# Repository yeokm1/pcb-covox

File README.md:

# pcb-covox
A tiny sound card based on the Covox Speech Thing design. I have another design which adds on an LM386 amplifier which can be found [here](https://github.com/yeokm1/pcb-covox-amp/).

##PCB Design software and addons used

1. Eagle 7.5.0: I use Standard but Light should still be able to open/modify the files.

##Images

This is a revision 3 board which has a bug in the mj2135 library which is a misaligned hole. I corrected this in Revision 4 but never actually fabricated that update.

Due to my oversight, only the DB25 pin 19 is grounded whearas the standard calls for pins 18-25 to be done so. You might need to modify the design if you face problems.

##Schematic drawings
Images are exported from Eagle at 600dpi.

##Parts required
Use Libreoffice to open [pcb-covox-bom.ods](pcb-covox-bom.ods)

##References
1. [Hardware implementation references](https://blog.frantovo.cz/c/307/DAC%20%28zvukov%C3%A1%20karta%29%20pro%20LPT%20port%20a.k.a.%20Covox)
2. [Design reference](http://kb.gr8bit.ru/KB0010/GR8BIT-KB0010-Adding-multimedia-capability-covox-device.html)
3. [MJ-2135 package obtained from coqui-dip](https://github.com/open-eie/coqui-dip)

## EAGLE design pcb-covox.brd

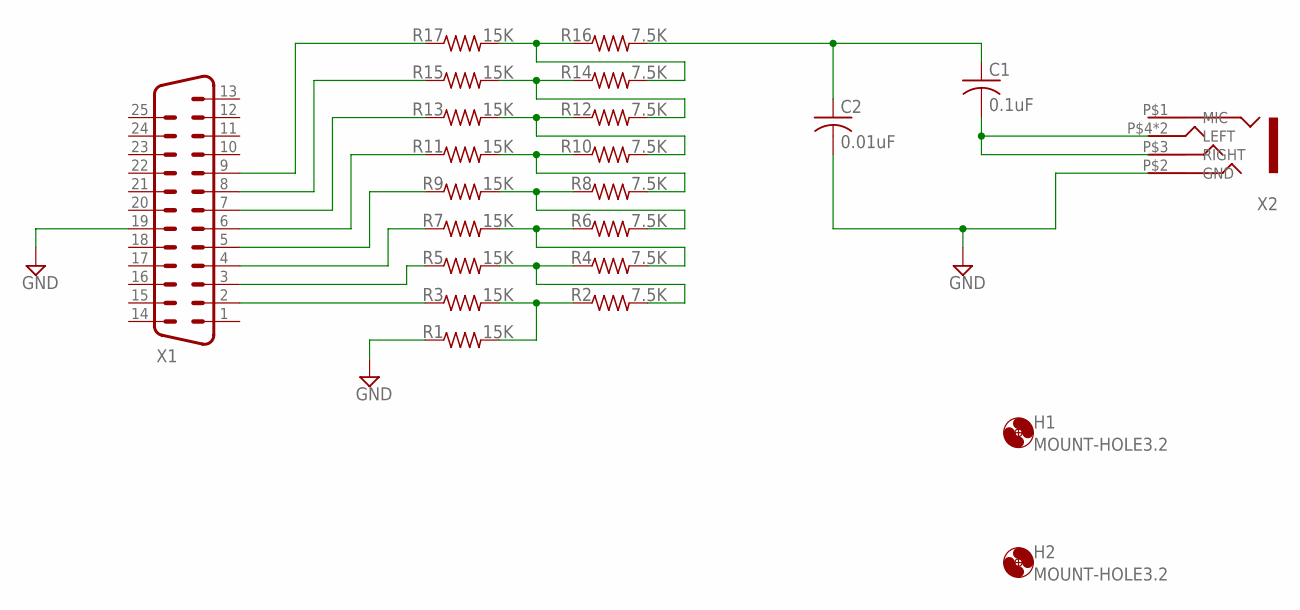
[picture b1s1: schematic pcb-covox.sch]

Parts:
C1: 0.1uF; C0805
C2: 0.01uF; C0805
H1, H2: MOUNT-HOLE3.2; 3,2
R1, R3, R5, R7, R9, R11, R13, R15, R17: 15K; R0805
R2, R4, R6, R8, R10, R12, R14, R16: 7.5K; R0805
X1: M25HP
X2: MJ-2135MJ-2135; MJ-2135

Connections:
GND: C2.2, R1.1, X1.19, X2.P$2 (GND)
unnamed: R3.1, X1.2
unnamed: R5.1, X1.3
unnamed: R7.1, X1.4
unnamed: R9.1, X1.5
unnamed: R11.1, X1.6
unnamed: R13.1, X1.7
unnamed: R15.1, X1.8
unnamed: R17.1, X1.9
unnamed: R1.2, R2.1, R3.2
unnamed: R2.2, R4.1, R5.2
unnamed: R4.2, R6.1, R7.2
unnamed: R6.2, R8.1, R9.2
unnamed: R8.2, R10.1, R11.2
unnamed: R10.2, R12.1, R13.2
unnamed: R12.2, R14.1, R15.2
unnamed: R14.2, R16.1, R17.2
unnamed: C1.1, C2.1, R16.2
unnamed: C1.2, X2.P$3 (RIGHT), X2.P$4 (LEFT), X2.P$5 (LEFT)

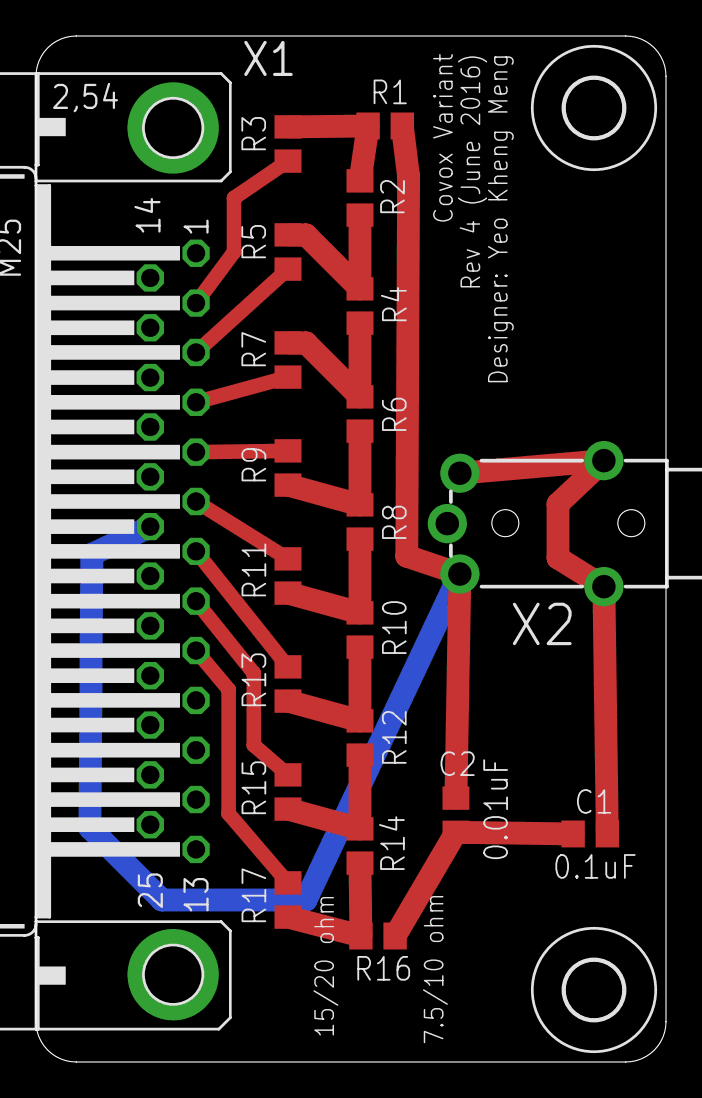
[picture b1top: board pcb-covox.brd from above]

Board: 2 copper layers, 35.0 x 57.0 mm, 23 parts (0 on the bottom side), 19 nets.

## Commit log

2016-04-14 rev 1
2016-04-14 images
2016-04-14 bom file
2016-04-27 corrected bug in size of audio connector
2016-04-29 correct drc error
2016-04-29 rev 2 gerber
2016-04-29 update to rev2 images
2016-04-29 adjust MJ-2135 value
2016-05-09 updated error in mj 2135 library
2016-05-09 rev 3 gerber
2016-05-09 update rev 3 image
2016-05-09 change directory of gerber
2016-06-17 update error in mj2135 lbr
2016-06-17 up to rev 4 for silkscreen
2016-07-02 rev4 board image
2016-07-02 rev4 gerber
2016-07-04 front image
2020-06-18 3d print model
